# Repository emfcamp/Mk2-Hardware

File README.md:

Hardware
========

Hardware for the TiLDA v2 Badge

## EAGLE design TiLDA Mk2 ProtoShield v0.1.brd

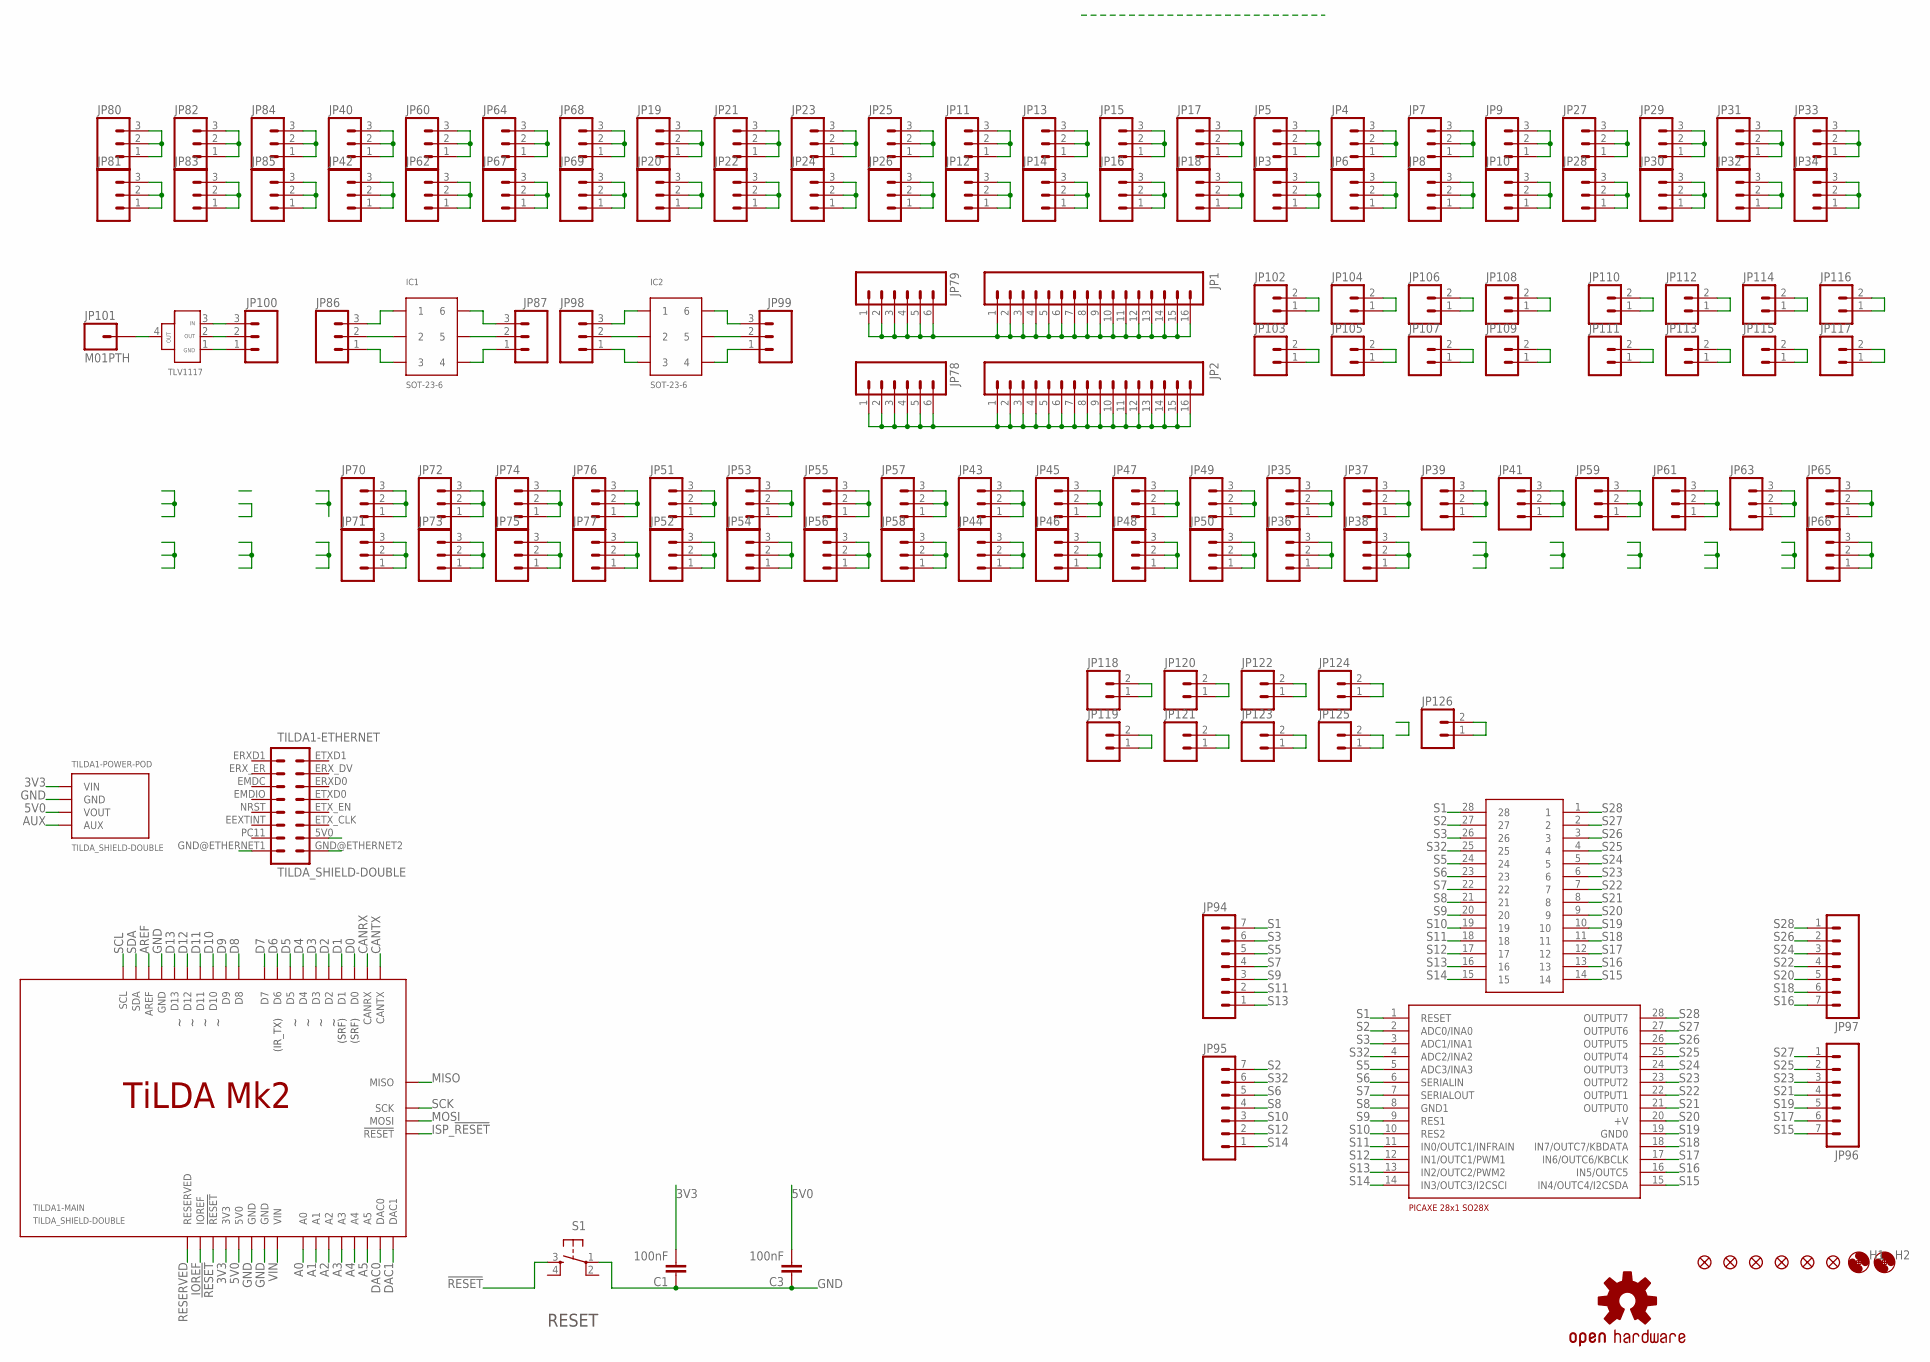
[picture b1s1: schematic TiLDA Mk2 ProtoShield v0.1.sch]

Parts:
C1, C3: 100nF; C025-024X044
FID1, FID2, FID3, FID4, FID5, FID6: FIDUCIAL1X2.5-STOP; FIDUCIAL-1X2.5-STOP
H1, H2: MOUNT-HOLE4.5-LWK; 4,5-LWK
IC1, IC2: SOT-23-6
JP1, JP2: M16PROTO_SILK; 1X16_PROTO_SILK
JP3, JP4, JP5, JP6, JP7, JP8, JP9, JP10, JP11, JP12, JP13, JP14, JP15, JP16, JP17, JP18, JP19, JP20, JP21, JP22, JP23, JP24, JP25, JP26, JP27, JP28, JP29, JP30, JP31, JP32, JP33, JP34, JP35, JP36, JP37, JP38, JP39, JP40, JP41, JP42, JP43, JP44, JP45, JP46, JP47, JP48, JP49, JP50, JP51, JP52, JP53, JP54, JP55, JP56, JP57, JP58, JP59, JP60, JP61, JP62, JP63, JP64, JP65, JP66, JP67, JP68, JP69, JP70, JP71, JP72, JP73, JP74, JP75, JP76, JP77, JP80, JP81, JP82, JP83, JP84, JP85: M03PROTO_SILK; 1X03_PROTO_SILK
JP78, JP79: M06PROTO_SILK; 1X06_PROTO_SLIK
JP86, JP87, JP98, JP99, JP100: M03PTH; 1X03
JP94, JP95, JP96, JP97: M07; 1X07
JP101: M01PTH; 1X01
JP102, JP103, JP104, JP105, JP106, JP107, JP108, JP109, JP110, JP111, JP112, JP113, JP114, JP115, JP116, JP117, JP118, JP119, JP120, JP121, JP122, JP123, JP124, JP125, JP126: M02PROTO_SILK; 1X02_PROTO_SILK
LOGO1: OSHW-LOGOM; OSHW-LOGO-M
LOGO2: EMFLOGO-2014-BOTH; EMFLOGO4
S1: TAC_SWITCHPTH; TACTILE-PTH
TILDA1: TILDA_SHIELD-DOUBLE; TILDA_SHIELD_DOUBLE
U$1: TLV1117-33CDCY; SOT223
U$2: SSOP28-NOSLIK; SSOP28D-NOSILK
U$5: PICAXE-28X1-SO28-MULITWIDE; S028-MUTLIWIDE

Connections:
3V3: C1.2, TILDA1.3V3@1 (3V3), TILDA1.3V3@2 (3V3), TILDA1.3V3@POD (VIN), TILDA1.3V3@POD1 (VIN)
5V0: C3.2, TILDA1.5V (5V0), TILDA1.5V0 (14), TILDA1.5V0@1 (5V0), TILDA1.5V0@POD (VOUT), TILDA1.5V0@POD1 (VOUT), TILDA1.5V@ISP (5V0), TILDA1.5V@ISP@1 (5V0)
!RESET: S1.3, TILDA1.!RESET, TILDA1.!RESET@1 (!RESET)
A0: TILDA1.A0, TILDA1.A0@1 (A0)
A1: TILDA1.A1, TILDA1.A1@1 (A1)
A2: TILDA1.A2, TILDA1.A2@1 (A2)
A3: TILDA1.A3, TILDA1.A3@1 (A3)
A4: TILDA1.A4, TILDA1.A4@1 (A4)
A5: TILDA1.A5, TILDA1.A5@1 (A5)
AREF: TILDA1.AREF, TILDA1.AREF@1 (AREF)
AUX: TILDA1.AUX@POD (AUX), TILDA1.AUX@POD1 (AUX)
CANRX: TILDA1.CANRX, TILDA1.CANRX@1 (CANRX)
CANTX: TILDA1.CANTX, TILDA1.CANTX@1 (CANTX)
D0: TILDA1.D0, TILDA1.D0@1 (D0)
D1: TILDA1.D1, TILDA1.D1@1 (D1)
D2: TILDA1.D2, TILDA1.D2@1 (D2)
D3: TILDA1.D3, TILDA1.D3@1 (D3)
D4: TILDA1.D4, TILDA1.D4@1 (D4)
D5: TILDA1.D5, TILDA1.D5@1 (D5)
D6: TILDA1.D6, TILDA1.D6@1 (D6)
D7: TILDA1.D7, TILDA1.D7@1 (D7)
D8: TILDA1.D8, TILDA1.D8@1 (D8)
D9: TILDA1.D9, TILDA1.D9@1 (D9)
D10: TILDA1.D10, TILDA1.D10@1 (D10)
D11: TILDA1.D11, TILDA1.D11@1 (D11)
D12: TILDA1.D12, TILDA1.D12@1 (D12)
D13: TILDA1.D13, TILDA1.D13@1 (D13)
DAC0: TILDA1.DAC0, TILDA1.DAC0@1 (DAC0)
DAC1: TILDA1.DAC1, TILDA1.DAC1@1 (DAC1)
GND: C1.1, C3.1, S1.1, TILDA1.GND@1 (GND), TILDA1.GND@2 (GND), TILDA1.GND@3 (GND), TILDA1.GND@4 (GND), TILDA1.GND@5 (GND), TILDA1.GND@6 (GND), TILDA1.GND@ETHERNET1 (15), TILDA1.GND@ETHERNET2 (16), TILDA1.GND@ISP (GND), TILDA1.GND@ISP1 (GND), TILDA1.GND@POD (GND), TILDA1.GND@POD1 (GND)
IOREF: TILDA1.IOREF, TILDA1.IOREF@1 (IOREF)
ISP_!RESET: TILDA1.!RESET@ISP (!RESET), TILDA1.!RESET@ISP1 (!RESET)
MISO: TILDA1.MISO, TILDA1.MISO@1 (MISO)
MOSI: TILDA1.MOSI, TILDA1.MOSI@1 (MOSI)
unnamed: JP1.1, JP1.2, JP1.3, JP1.4, JP1.5, JP1.6, JP1.7, JP1.8, JP1.9, JP1.10, JP1.11, JP1.12, JP1.13, JP1.14, JP1.15, JP1.16, JP79.1, JP79.2, JP79.3, JP79.4, JP79.5, JP79.6
unnamed: JP2.1, JP2.2, JP2.3, JP2.4, JP2.5, JP2.6, JP2.7, JP2.8, JP2.9, JP2.10, JP2.11, JP2.12, JP2.13, JP2.14, JP2.15, JP2.16, JP78.1, JP78.2, JP78.3, JP78.4, JP78.5, JP78.6
unnamed: JP5.1, JP5.2, JP5.3
unnamed: JP3.1, JP3.2, JP3.3
unnamed: JP4.1, JP4.2, JP4.3
unnamed: JP6.1, JP6.2, JP6.3
unnamed: JP7.1, JP7.2, JP7.3
unnamed: JP8.1, JP8.2, JP8.3
unnamed: JP9.1, JP9.2, JP9.3
unnamed: JP10.1, JP10.2, JP10.3
unnamed: JP11.1, JP11.2, JP11.3
unnamed: JP12.1, JP12.2, JP12.3
unnamed: JP13.1, JP13.2, JP13.3
unnamed: JP14.1, JP14.2, JP14.3
unnamed: JP15.1, JP15.2, JP15.3
unnamed: JP16.1, JP16.2, JP16.3
unnamed: JP17.1, JP17.2, JP17.3
unnamed: JP18.1, JP18.2, JP18.3
unnamed: JP19.1, JP19.2, JP19.3
unnamed: JP20.1, JP20.2, JP20.3
unnamed: JP21.1, JP21.2, JP21.3
unnamed: JP22.1, JP22.2, JP22.3
unnamed: JP23.1, JP23.2, JP23.3
unnamed: JP24.1, JP24.2, JP24.3
unnamed: JP25.1, JP25.2, JP25.3
unnamed: JP26.1, JP26.2, JP26.3
unnamed: JP27.1, JP27.2, JP27.3
unnamed: JP28.1, JP28.2, JP28.3
unnamed: JP29.1, JP29.2, JP29.3
unnamed: JP30.1, JP30.2, JP30.3
unnamed: JP31.1, JP31.2, JP31.3
unnamed: JP32.1, JP32.2, JP32.3
unnamed: JP33.1, JP33.2, JP33.3
unnamed: JP34.1, JP34.2, JP34.3
unnamed: JP35.1, JP35.2, JP35.3
unnamed: JP36.1, JP36.2, JP36.3
unnamed: JP37.1, JP37.2, JP37.3
unnamed: JP38.1, JP38.2, JP38.3
unnamed: JP39.1, JP39.2, JP39.3
unnamed: JP41.1, JP41.2, JP41.3
unnamed: JP43.1, JP43.2, JP43.3
unnamed: JP44.1, JP44.2, JP44.3
unnamed: JP45.1, JP45.2, JP45.3
unnamed: JP46.1, JP46.2, JP46.3
unnamed: JP47.1, JP47.2, JP47.3
unnamed: JP48.1, JP48.2, JP48.3
unnamed: JP49.1, JP49.2, JP49.3
unnamed: JP50.1, JP50.2, JP50.3
unnamed: JP51.1, JP51.2, JP51.3
unnamed: JP52.1, JP52.2, JP52.3
unnamed: JP53.1, JP53.2, JP53.3
unnamed: JP54.1, JP54.2, JP54.3
unnamed: JP55.1, JP55.2, JP55.3
unnamed: JP56.1, JP56.2, JP56.3
unnamed: JP57.1, JP57.2, JP57.3
unnamed: JP58.1, JP58.2, JP58.3
unnamed: JP59.1, JP59.2, JP59.3
unnamed: JP61.1, JP61.2, JP61.3
unnamed: JP63.1, JP63.2, JP63.3
unnamed: JP65.1, JP65.2, JP65.3
unnamed: JP66.1, JP66.2, JP66.3
unnamed: JP40.1, JP40.2, JP40.3
unnamed: JP42.1, JP42.2, JP42.3
unnamed: JP60.1, JP60.2, JP60.3
unnamed: JP62.1, JP62.2, JP62.3
unnamed: JP64.1, JP64.2, JP64.3
unnamed: JP67.1, JP67.2, JP67.3
unnamed: JP68.1, JP68.2, JP68.3
unnamed: JP69.1, JP69.2, JP69.3
unnamed: JP70.1, JP70.2, JP70.3
unnamed: JP71.1, JP71.2, JP71.3
unnamed: JP72.1, JP72.2, JP72.3
unnamed: JP73.1, JP73.2, JP73.3
unnamed: JP74.1, JP74.2, JP74.3
unnamed: JP75.1, JP75.2, JP75.3
unnamed: JP76.1, JP76.2, JP76.3
unnamed: JP77.1, JP77.2, JP77.3
unnamed: IC1.2, JP86.2
unnamed: IC1.1, JP86.3
unnamed: JP80.1, JP80.2, JP80.3
unnamed: JP81.1, JP81.2, JP81.3
unnamed: JP82.1, JP82.2, JP82.3
unnamed: JP83.1, JP83.2, JP83.3
unnamed: JP84.1, JP84.2, JP84.3
unnamed: JP85.1, JP85.2, JP85.3
unnamed: IC1.3, JP86.1
unnamed: IC1.5, JP87.2
unnamed: IC1.6, JP87.3
unnamed: IC1.4, JP87.1
unnamed: IC2.2, JP98.2
unnamed: IC2.1, JP98.3
unnamed: IC2.3, JP98.1
unnamed: IC2.5, JP99.2
unnamed: IC2.6, JP99.3
unnamed: IC2.4, JP99.1
unnamed: JP100.1, U$1.1 (GND)
unnamed: JP100.2, U$1.2 (OUT1)
unnamed: JP100.3, U$1.3 (IN)
unnamed: JP101.1, U$1.4 (OUT2)
unnamed: JP102.1, JP102.2
unnamed: JP103.1, JP103.2
unnamed: JP104.1, JP104.2
unnamed: JP105.1, JP105.2
unnamed: JP106.1, JP106.2
unnamed: JP107.1, JP107.2
unnamed: JP108.1, JP108.2
unnamed: JP109.1, JP109.2
unnamed: JP110.1, JP110.2
unnamed: JP111.1, JP111.2
unnamed: JP112.1, JP112.2
unnamed: JP113.1, JP113.2
unnamed: JP114.1, JP114.2
unnamed: JP115.1, JP115.2
unnamed: JP116.1, JP116.2
unnamed: JP117.1, JP117.2
unnamed: JP118.1, JP118.2
unnamed: JP119.1, JP119.2
unnamed: JP120.1, JP120.2
unnamed: JP121.1, JP121.2
unnamed: JP122.1, JP122.2
unnamed: JP123.1, JP123.2
unnamed: JP124.1, JP124.2
unnamed: JP125.1, JP125.2
unnamed: JP126.1, JP126.2
RESERVED: TILDA1.RESERVED, TILDA1.RESERVED@1 (RESERVED)
S1: JP94.7, U$2.28, U$5.1 (RESET)
S2: JP95.7, U$2.27, U$5.2 (ADC0/INA0)
S3: JP94.6, U$2.26, U$5.3 (ADC1/INA1)
S5: JP94.5, U$2.24, U$5.5 (ADC3/INA3)
S6: JP95.5, U$2.23, U$5.6 (SERIALIN)
S7: JP94.4, U$2.22, U$5.7 (SERIALOUT)
S8: JP95.4, U$2.21, U$5.8 (GND1)
S9: JP94.3, U$2.20, U$5.9 (RES1)
S10: JP95.3, U$2.19, U$5.10 (RES2)
S11: JP94.2, U$2.18, U$5.11 (IN0/OUTC1/INFRAIN)
S12: JP95.2, U$2.17, U$5.12 (IN1/OUTC1/PWM1)
S13: JP94.1, U$2.16, U$5.13 (IN2/OUTC2/PWM2)
S14: JP95.1, U$2.15, U$5.14 (IN3/OUTC3/I2CSCI)
S15: JP96.7, U$2.14, U$5.15 (IN4/OUTC4/I2CSDA)
S16: JP97.7, U$2.13, U$5.16 (IN5/OUTC5)
S17: JP96.6, U$2.12, U$5.17 (IN6/OUTC6/KBCLK)
S18: JP97.6, U$2.11, U$5.18 (IN7/OUTC7/KBDATA)
S19: JP96.5, U$2.10, U$5.19 (GND0)
S20: JP97.5, U$2.9, U$5.20 (+V)
S21: JP96.4, U$2.8, U$5.21 (OUTPUT0)
S22: JP97.4, U$2.7, U$5.22 (OUTPUT1)
S23: JP96.3, U$2.6, U$5.23 (OUTPUT2)
S24: JP97.3, U$2.5, U$5.24 (OUTPUT3)
S25: JP96.2, U$2.4, U$5.25 (OUTPUT4)
S26: JP97.2, U$2.3, U$5.26 (OUTPUT5)
S27: JP96.1, U$2.2, U$5.27 (OUTPUT6)
S28: JP97.1, U$2.1, U$5.28 (OUTPUT7)
S32: JP95.6, U$2.25, U$5.4 (ADC2/INA2)
SCK: TILDA1.SCK, TILDA1.SCK@1 (SCK)
SCL: TILDA1.SCL, TILDA1.SCL@1 (SCL)
SDA: TILDA1.SDA, TILDA1.SDA@1 (SDA)
VIN: TILDA1.VIN, TILDA1.VIN@1 (VIN)

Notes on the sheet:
RESET

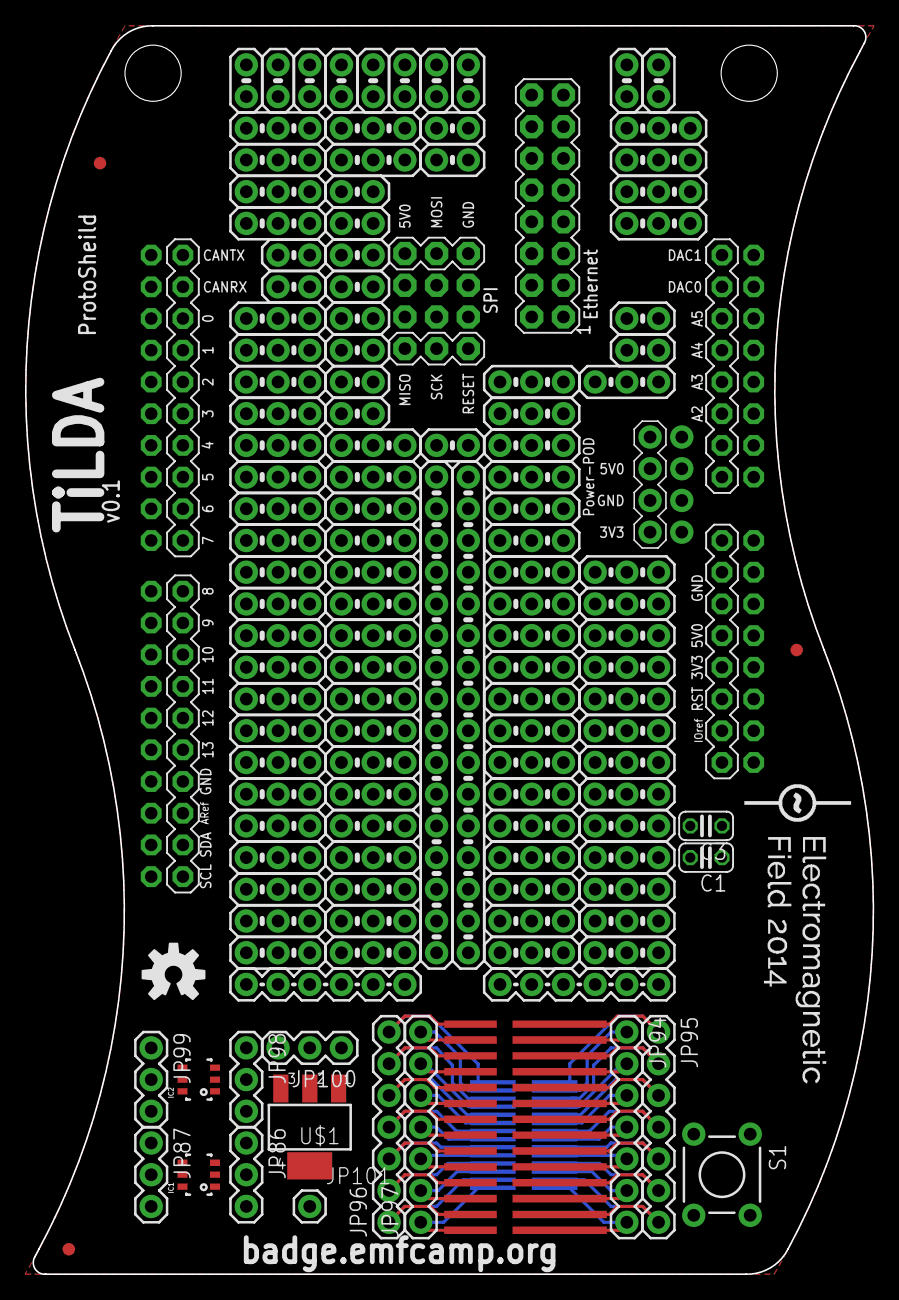
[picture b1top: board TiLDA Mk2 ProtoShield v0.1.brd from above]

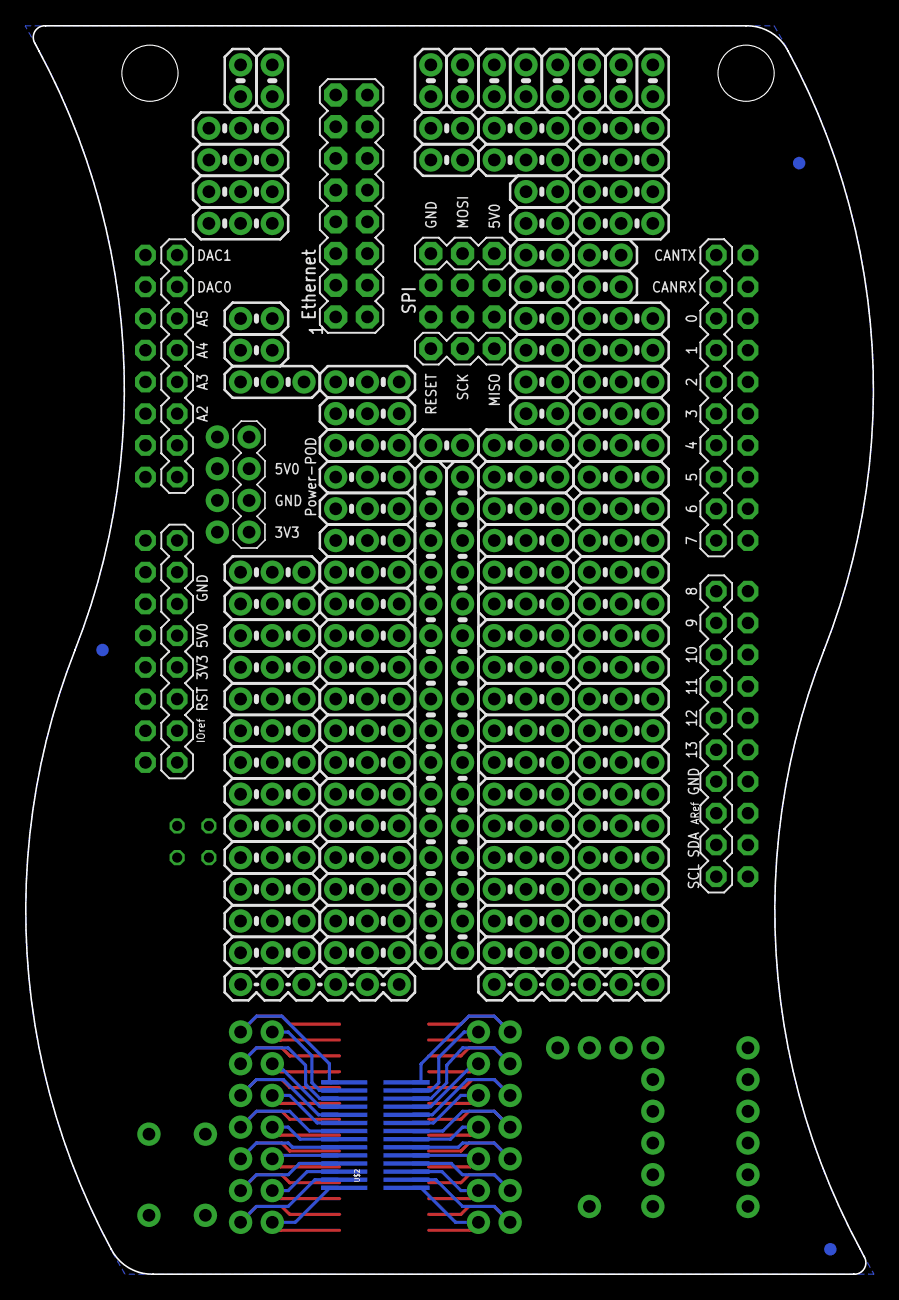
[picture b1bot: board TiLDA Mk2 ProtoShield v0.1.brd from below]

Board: 4 copper layers, 67.9 x 100.0 mm, 139 parts (4 on the bottom side), 191 nets.

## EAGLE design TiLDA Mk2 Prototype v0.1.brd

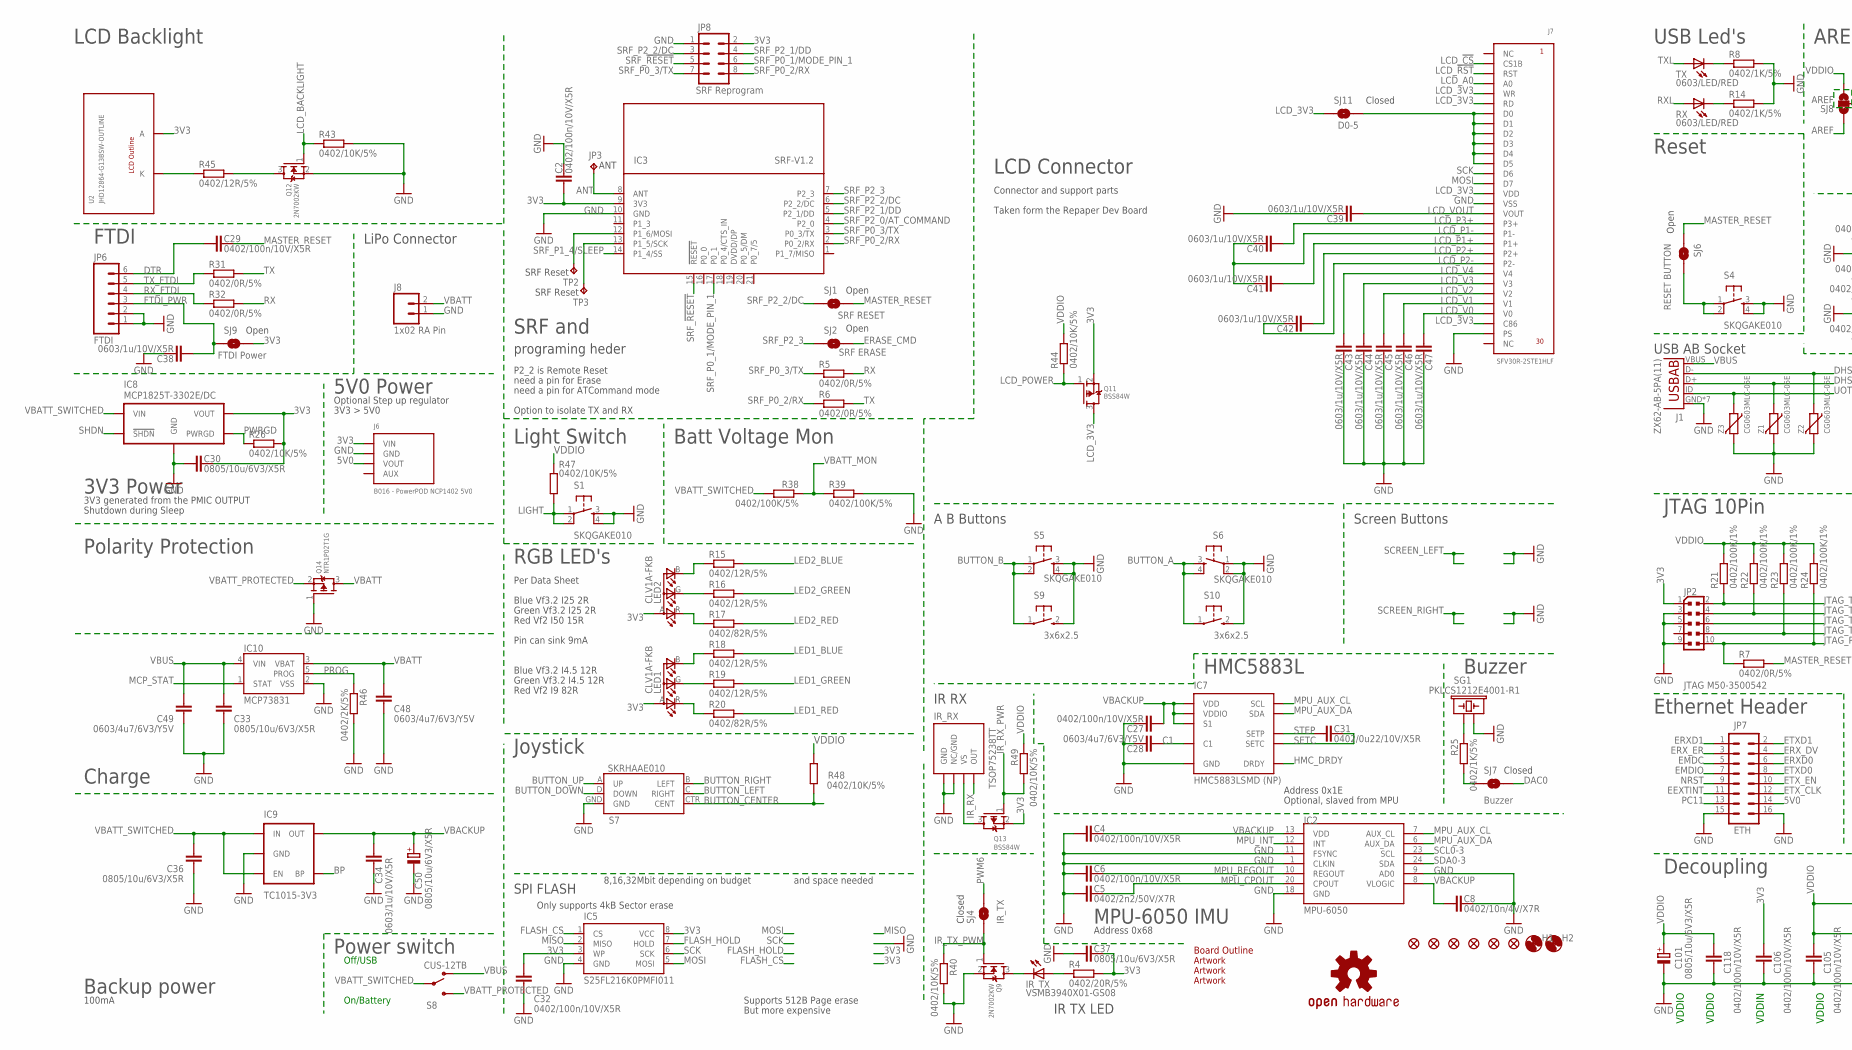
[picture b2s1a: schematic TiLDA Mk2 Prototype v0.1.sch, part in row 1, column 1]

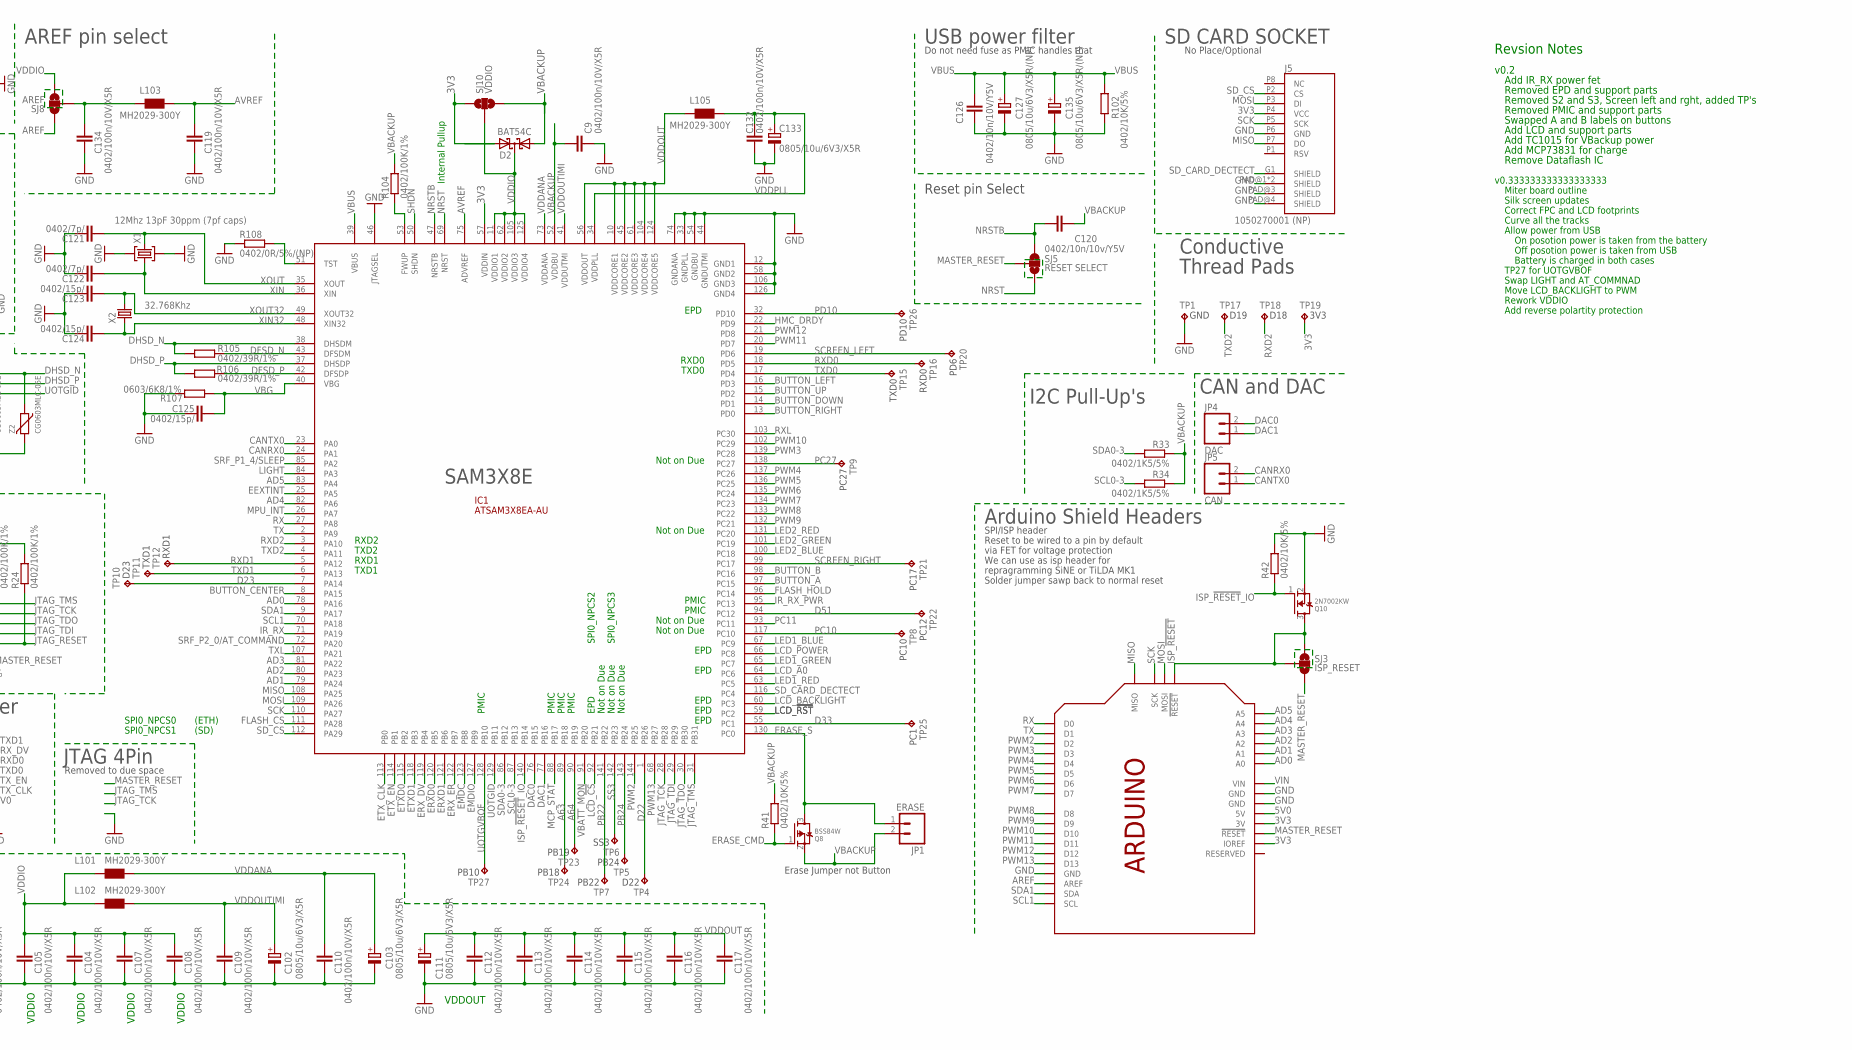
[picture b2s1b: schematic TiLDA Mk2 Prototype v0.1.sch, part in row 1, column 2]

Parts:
ARTWORK1: ARTWORK_FRONT1; TILDA_ARTWORK_FRONT1
ARTWORK2: ARTWORK_ACHIEVEMENT2; TILDA_ARTWORK_ACHIEVEMENT2
ARTWORK3: ARTWORK_ACHIEVEMENT3; TILDA_ARTWORK_ACHIEVEMENT3
C2, C4, C6, C9, C27, C29, C32, C104, C105, C106, C107, C108, C109, C110, C112, C113, C114, C115, C116, C117, C118, C119, C132, C134: 0402/100n/10V/X5R; C0402-ARDUINO-ROUND
C5: 0402/2n2/50V/X7R; C0402-ARDUINO-ROUND
C8: 0402/10n/4V/X7R; C0402-ARDUINO-ROUND
C28, C48, C49: 0603/4u7/6V3/Y5V; C0603-ROUND
C30, C33, C36, C37: 0805/10u/6V3/X5R; C0805RND
C31: 0402/0u22/10V/X5R; C0402-ARDUINO-ROUND
C34, C38, C39, C40, C41, C42, C43, C44, C45, C46, C47: 0603/1u/10V/X5R; C0603-ROUND
C50, C101, C102, C103, C111, C133: 0805/10u/6V3/X5R; C0805RNDPOL
C120: 0402/10n/10v/Y5V; C0402-ARDUINO-ROUND
C121, C122: 0402/7p/; C0402-ARDUINO-ROUND
C123, C124, C125: 0402/15p/; C0402-ARDUINO-ROUND
C126: 0402/10n/10V/Y5V; C0402-ARDUINO-ROUND
C127, C135: 0805/10u/6V3/X5R/(NP); C0805RNDPOL
D2: BAT54C; SOT23
FID1, FID2, FID3, FID4, FID5, FID6: FIDUCIAL1X2.5-STOP; FIDUCIAL-1X2.5-STOP
H1, H2: MOUNT-HOLE4.5-LWK; 4,5-LWK
IC1: ATSAM3X8EA-AU; LQFP144
IC2: MPU-6050; QFN-24-NODIE
IC3: SRF-V1.2; SRF-LANDING-1.2
IC5: S25FL216K0PMFI011; SO08-EIAJ
IC7: HMC5883LSMD (NP); 16LPCC
IC8: MCP1825T-3302E/DC; SOT127P700X180-6N
IC9: TC1015-3V3; SOT23-5
IC10: MCP73831; SOT23-5
IR_RX: TSOP75238TT; TSOP75X
IR_TX: VSMB3940X01-GS08; P-LCC-2
J1: ZX62-AB-5PA(11); USB-AB-MICRO-SMD_LWK
J3: Arduino Headers; ARDUINOR3-LWKTXT-REF-SPI
J5: 1050270001 (NP); 105027-LWK
J6: B016 - PowerPOD NCP1402 5V0; POWER-POD-EMF
J7: SFV30R-2STE1HLF
J8: 1x02 RA Pin; 1X02_RA
JP1: ERASE; 1X02
JP2: JTAG M50-3500542; PINHEAD_2X05_127
JP3: ANT; P1-13
JP4: DAC; 1X02_NO_SILK_OCT
JP5: CAN; 1X02_NO_SILK_OCT
JP6: FTDI; 1X06
JP7: ETH; 2X8
JP8: SRF Reprogram; 2X4-PAD
L101, L102, L103, L105: MH2029-300Y; WUERTH-0805
LED1, LED2: CLV1A-FKB; LED-RGB_CLV1A-FKB
LOGO1: OSHW-LOGOM; OSHW-LOGO-M
OUTLINE1: TILDA_BOARDOUTLINE-MITER; TILDA_BADGEBOARDBARE-VERYWIDE-MITER
Q8, Q11, Q13: BSS84W; SC70-3-R
Q9, Q10, Q12: 2N7002KW; SC70-3-R
Q14: NTR1P02T1G; SOT23-R
R4: 0402/20R/5%; R0402-ARDUINO-ROUND
R5, R6, R7, R31, R32: 0402/0R/5%; R0402-ARDUINO-ROUND
R8, R14, R25: 0402/1K/5%; R0402-ARDUINO-ROUND
R15, R16, R18, R19, R45: 0402/12R/5%; R0402-ARDUINO-ROUND
R17, R20: 0402/82R/5%; R0402-ARDUINO-ROUND
R21, R22, R23, R24, R104: 0402/100K/1%; R0402-ARDUINO-ROUND
R26, R40, R41, R42, R43, R44, R47, R48, R49, R102: 0402/10K/5%; R0402-ARDUINO-ROUND
R33, R34: 0402/1K5/5%; R0402-ARDUINO-ROUND
R38, R39: 0402/100K/5%; R0402-ARDUINO-ROUND
R46: 0402/2K/5%; R0402-ARDUINO-ROUND
R105, R106: 0402/39R/1%; R0402-ARDUINO-ROUND
R107: 0603/6K8/1%; R0603-ROUND
R108: 0402/0R/5%/(NP); R0402-ARDUINO-ROUND
RX: 0603/LED/RED; LED-0805-CORRECT
S1, S4, S5, S6: SKQGAKE010; TACTILE_SWITCH_SMD
S7: SKRHAAE010; JOYSTICK_MULTICOMP
S8: CUS-12TB; SWITCH-SPST-SMD-A
S9, S10: 3x6x2.5; TACTILE_SWITCH_SMD_3X6X2.5H
SG1: PKLCS1212E4001-R1; BUZZER-PKLCS1212E
SJ1: SRF RESET; SJ_2S-NO
SJ2: SRF ERASE; SJ_2S-NO
SJ3: ISP_RESET; SJ_3
SJ4: IR_TX; SJ_2S-TRACE
SJ5: RESET SELECT; SJ_3
SJ6: RESET BUTTON; SJ_2S-NO
SJ7: Buzzer; SJ_2S-TRACE
SJ8: AREF; SJ_3
SJ9: FTDI Power; SJ_2S-NO
SJ10: VDDIO; SJ_3
SJ11: D0-5; SJ_2S-NO
TP1: GND; P1-13
TP2, TP3: SRF Reset; B1,27
TP4: D22; B1,27
TP5: PB24; B1,27
TP6: SS3; B1,27
TP7: PB22; B1,27
TP8: PC10; B1,27
TP9: PC27; B1,27
TP10: D23; B1,27
TP11: TXD1; B1,27
TP12: RXD1; B1,27
TP15: TXD0; B1,27
TP16: RXD0; B1,27
TP17: D19; P1-13
TP18: D18; P1-13
TP19: 3V3; P1-13
TP20: PD6; B1,27
TP21: PC17; B1,27
TP22: PC12; B1,27
TP23: PB19; B1,27
TP24: PB18; B1,27
TP25: PC1; B1,27
TP26: PD10; B1,27
TP27: PB10; B1,27
TX: 0603/LED/RED; LED-0805-CORRECT
U2: JHD12864-G13BSW-OUTLINE
X1: 12Mhz 13pF 30ppm (7pf caps); CRYSTAL-5X3.2
X2: 32.768Khz; RESONATOR_EPSON_FC_145
Z1, Z2, Z3: CG0603MLC-05E; CT/CN0603

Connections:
3V3: C2.2, C30.1, C32.2, C37.1, C106.2, D2.2 (A2), IC1.57 (VDDIN), IC3.9 (3V3), IC5.3 (WP), IC5.8 (VCC), IC8.4 (VOUT), J3.3V, J3.IOREF, J5.P4 (VCC), J6.1 (VIN), JP2.1, JP8.2, LED1.A (ANODE), LED2.A (ANODE), Q11.2 (S), Q13.2 (S), R4.2, R26.2, SJ9.2, SJ10.1, TP19.TP, U2.A
5V0: J3.5V, J3.5V@ISP (5V), J6.3 (VOUT), JP7.14
A63: IC1.89 (PB18), TP24.TP
A64: IC1.90 (PB19), TP23.TP
AD0: IC1.78 (PA16), J3.A0
AD1: IC1.79 (PA24), J3.A1
AD2: IC1.80 (PA23), J3.A2
AD3: IC1.81 (PA22), J3.A3
AD4: IC1.82 (PA6), J3.A4
AD5: IC1.83 (PA4), J3.A5
ANT: IC3.8 (ANT), JP3.TP
AREF: J3.AREF, SJ8.1
AVREF: C119.2, IC1.75 (ADVREF), L103.2
BP: IC9.4 (BP)
BUTTON_A: IC1.97 (PC15), S6.3, S6.4, S10.1
BUTTON_B: IC1.98 (PC16), S5.1, S5.2, S9.1
BUTTON_CENTER: IC1.8 (PA15), R48.1, S7.CTR (CENT)
BUTTON_DOWN: IC1.14 (PD1), S7.D (DOWN)
BUTTON_LEFT: IC1.16 (PD3), S7.C (RIGHT)
BUTTON_RESET: S4.1, S4.2, SJ6.2
BUTTON_RIGHT: IC1.13 (PD0), S7.B (LEFT)
BUTTON_UP: IC1.15 (PD2), S7.A (UP)
BUZZER+: R25.1, SG1.P$1 (1)
BUZZER_RES: R25.2, SJ7.1
C1: C28.2, IC7.10 (C1)
CANRX0: IC1.24 (PA1), JP5.2
CANTX0: IC1.23 (PA0), JP5.1
D22: IC1.1 (PB26), TP4.TP
D23: IC1.7 (PA14), TP10.TP
D33: IC1.55 (PC1), TP25.TP
D51: IC1.94 (PC12), TP22.TP
DAC0: IC1.76 (PB15), JP4.2, SJ7.2
DAC1: IC1.77 (PB16), JP4.1
DFSD_N: IC1.43 (DFSDM), R105.2
DFSD_P: IC1.42 (DFSDP), R106.2
DHSD_N: IC1.38 (DHSDM), J1.D-, R105.1, Z2.1
DHSD_P: IC1.37 (DHSDP), J1.D+, R106.1, Z1.1
DTR: C29.2, JP6.6
EEXTINT: IC1.25 (PA5), JP7.11
EMDC: IC1.123 (PB8), JP7.5
EMDIO: IC1.127 (PB9), JP7.7
ERASE_CMD: Q8.1 (G), R41.1, SJ2.2
ERASE_S: IC1.130 (PC0), JP1.1, Q8.3 (D)
ERXD0: IC1.120 (PB5), JP7.6
ERXD1: IC1.121 (PB6), JP7.1
ERX_DV: IC1.119 (PB4), JP7.4
ERX_ER: IC1.122 (PB7), JP7.3
ETXD0: IC1.115 (PB2), JP7.8
ETXD1: IC1.118 (PB3), JP7.2
ETX_CLK: IC1.113 (PB0), JP7.12
ETX_EN: IC1.114 (PB1), JP7.10
FLASH_CS: IC1.111 (PA28), IC5.1 (CS)
FLASH_HOLD: IC1.96 (PC14), IC5.7 (HOLD)
FTDI_PWR: C38.2, JP6.3, SJ9.1
FWUP: IC1.53 (FWUP), R104.1
GND: C2.1, C4.2, C5.2, C6.2, C8.1, C9.1, C27.1, C28.1, C30.2, C32.1, C33.1, C34.1, C36.1, C37.2, C38.1, C39.1, C43.1, C44.1, C45.1, C46.1, C47.1, C48.1, C49.1, C50.-, C101.-, C102.-, C103.-, C104.1, C105.1, C106.1, C107.1, C108.1, C109.1, C110.1, C111.-, C112.1, C113.1, C114.1, C115.1, C116.1, C117.1, C118.1, C119.1, C121.1, C122.1, C123.1, C124.1, C125.1, C126.2, C127.-, C132.2, C133.-, C134.1, C135.-, IC1.12 (GND1), IC1.33 (GNDPLL), IC1.44 (GNDUTMI), IC1.46 (JTAGSEL), IC1.54 (GNDBU), IC1.58 (GND2), IC1.74 (GNDANA), IC1.106 (GND3), IC1.126 (GND4), IC2.1 (CLKIN), IC2.9 (AD0), IC2.11 (FSYNC), IC2.18 (GND), IC3.10 (GND), IC5.4 (GND), IC7.9 (GND), IC7.11 (GND), IC8.3 (GND), IC8.6 (GND), IC9.2 (GND), IC10.2 (VSS), IR_RX.1 (GND), IR_RX.4 (NC/GND), J1.GND, J1.P$1 (GND), J1.P$2 (GND), J1.P$6 (GND), J1.P$7 (GND), J1.P$8 (GND), J1.P$9 (GND), J3.GND@1 (GND), J3.GND@2 (GND), J3.GND@3 (GND), J3.GND@ISP (GND), J5.P6 (GND), J5.PAD@1 (SHIELD), J5.PAD@2 (SHIELD), J5.PAD@3 (SHIELD), J5.PAD@4 (SHIELD), J6.2 (GND), J7.16 (VSS), J7.29 (PS), J7.M1 (VSS), J7.M2 (VSS), J8.1, JP2.3, JP2.5, JP2.9, JP6.1, JP6.2, JP7.15, JP7.16, JP8.1, Q9.2 (S), Q10.2 (S), Q12.2 (S), Q14.1 (G), R8.2, R14.2, R39.2, R40.2, R42.2, R43.2, R46.2, R102.1, R107.2, R108.1, S1.3, S1.4, S4.3, S4.4, S5.3, S5.4, S6.1, S6.2, S7.GND, S9.2 (3), S10.2 (3), SG1.P$2 (2), TP1.TP, X1.2 (GND), X1.4 (GND), Z1.2, Z2.2, Z3.2
HMC_DRDY: IC1.22 (PD9), IC7.15 (DRDY)
IR_RX: IC1.71 (PA19), IR_RX.3 (OUT)
IR_RX_PWR: IC1.95 (PC13), Q13.1 (G), R49.2
IR_TX_A: IR_TX.A, R4.1
IR_TX_C: IR_TX.C, Q9.3 (D)
IR_TX_PWM: Q9.1 (G), R40.1, SJ4.1
ISP_!RESET: J3.!RESET@ISP (!RESET), Q10.3 (D), SJ3.1, SJ3.2
ISP_!RESET!_IO: IC1.140 (PB14), Q10.1 (G), R42.1
JTAG_RESET: JP2.10, R7.1, R24.1
JTAG_TCK: IC1.28 (PB28), JP2.4, R22.1
JTAG_TDI: IC1.29 (PB29), JP2.8, R23.1
JTAG_TDO: IC1.30 (PB30), JP2.6
JTAG_TMS: IC1.31 (PB31), JP2.2, R21.1
LCD_3V3: J7.5 (WR), J7.6 (RD), J7.15 (VDD), J7.28 (C86), Q11.3 (D), SJ11.1
LCD_!CS: IC1.92 (PB21), J7.2 (CS1B)
LCD_!RST: IC1.59 (PC2), J7.3 (RST)
LCD_A0: IC1.64 (PC6), J7.4 (A0)
LCD_A_SWITCHED: Q12.3 (D), R45.2
LCD_BACKLIGHT: IC1.60 (PC3), Q12.1 (G), R43.1
LCD_P1+: C41.2, J7.20 (P1+)
LCD_P1-: C40.1, C41.1, J7.19 (P1-)
LCD_P2+: C42.2, J7.21 (P2+)
LCD_P2-: C42.1, J7.22 (P2-)
LCD_P3+: C40.2, J7.18 (P3+)
LCD_POWER: IC1.66 (PC8), Q11.1 (G), R44.1
LCD_V0: C47.2, J7.27 (V0)
LCD_V1: C46.2, J7.26 (V1)
LCD_V2: C45.2, J7.25 (V2)
LCD_V3: C44.2, J7.24 (V3)
LCD_V4: C43.2, J7.23 (V4)
LCD_VOUT: C39.2, J7.17 (VOUT)
LED1_BLUE: IC1.67 (PC9), R18.2
LED1_GREEN: IC1.65 (PC7), R19.2
LED1_RED: IC1.63 (PC5), R20.2
LED2_BLUE: IC1.100 (PC18), R15.2
LED2_GREEN: IC1.101 (PC19), R16.2
LED2_RED: IC1.131 (PC20), R17.2
LIGHT: IC1.84 (PA3), R47.1, S1.1, S1.2
MASTER_RESET: C29.1, J3.!RESET, R7.2, SJ1.2, SJ3.3, SJ5.2, SJ6.1
MCP_STAT: IC1.88 (PB17), IC10.1 (STAT)
MISO: IC1.108 (PA25), IC5.2 (MISO), J3.MISO, J5.P7 (DO)
MOSI: IC1.109 (PA26), IC5.5 (MOSI), J3.MOSI, J5.P3 (DI), J7.14 (D7)
MPU_AUX_CL: IC2.7 (AUX_CL), IC7.1 (SCL)
MPU_AUX_DA: IC2.6 (AUX_DA), IC7.16 (SDA)
MPU_CPOUT: C5.1, IC2.20 (CPOUT)
MPU_INT: IC1.26 (PA7), IC2.12 (INT)
MPU_REGOUT: C6.1, IC2.10 (REGOUT)
unnamed: R45.1, U2.K
unnamed: R8.1, TX.C
unnamed: R14.1, RX.C
unnamed: J7.7 (D0), J7.8 (D1), J7.9 (D2), J7.10 (D3), J7.11 (D4), J7.12 (D5), SJ11.2
unnamed: LED1.R (CRED), R20.1
unnamed: LED1.G (CGREEN), R19.1
unnamed: LED1.B (CBLUE), R18.1
unnamed: LED2.R (CRED), R17.1
unnamed: LED2.G (CGREEN), R16.1
unnamed: C134.2, L103.1, SJ8.2
unnamed: LED2.B (CBLUE), R15.1
unnamed: IR_RX.2 (VS), Q13.3 (D)
unnamed: IC3.12 (P1_6/MOSI), TP2.TP
unnamed: IC3.13 (P1_5/SCK), TP3.TP
NRST: IC1.69 (NRST), JP7.9, SJ5.3
NRSTB: C120.2, IC1.47 (NRSTB), SJ5.1
PB22: IC1.141 (PB22), TP7.TP
PB24: IC1.143 (PB24), TP5.TP
PC10: IC1.117 (PC10), TP8.TP
PC11: IC1.93 (PC11), JP7.13
PC27: IC1.138 (PC27), TP9.TP
PD10: IC1.32 (PD10), TP26.TP
PROG: IC10.5 (PROG), R46.1
PWM2: IC1.144 (PB25), J3.D2
PWM3: IC1.139 (PC28), J3.D3
PWM4: IC1.137 (PC26), J3.D4
PWM5: IC1.136 (PC25), J3.D5
PWM6: IC1.135 (PC24), J3.D6, SJ4.2
PWM7: IC1.134 (PC23), J3.D7
PWM8: IC1.133 (PC22), J3.D8
PWM9: IC1.132 (PC21), J3.D9
PWM10: IC1.102 (PC29), J3.D10
PWM11: IC1.20 (PD7), J3.D11
PWM12: IC1.21 (PD8), J3.D12
PWM13: IC1.68 (PB27), J3.D13
PWRGD: IC8.5 (PWRGD), R26.1
RX: IC1.27 (PA8), J3.D0, R5.2, R32.2
RXD0: IC1.18 (PD5), TP16.TP
RXD1: IC1.5 (PA12), TP12.TP
RXD2: IC1.3 (PA10), TP18.TP
RXL: IC1.103 (PC30), RX.A
RX_FTDI: JP6.4, R32.1
SCK: IC1.110 (PA27), IC5.6 (SCK), J3.SCK, J5.P5 (SCK), J7.13 (D6)
SCL0-3: IC1.87 (PB13), IC2.23 (SCL), R34.2
SCL1: IC1.70 (PA18), J3.SCL
SCREEN_LEFT: IC1.19 (PD6), TP20.TP
SCREEN_RIGHT: IC1.99 (PC17), TP21.TP
SDA0-3: IC1.86 (PB12), IC2.24 (SDA), R33.2
SDA1: IC1.9 (PA17), J3.SDA
SD_CARD_DECTECT: IC1.116 (PC4), J5.G1 (SHIELD)
SD_CS: IC1.112 (PA29), J5.P2 (CS)
SETC: C31.1, IC7.12 (SETC)
SHDN: IC1.50 (SHDN), IC8.1 (!SHDN)
SRF_!RESET: IC3.15 (!RESET), JP8.5
SRF_P0_1/MODE_PIN_1: IC3.17 (P0_1), JP8.6
SRF_P0_2/RX: IC3.2 (P0_2/RX), JP8.8, R6.1
SRF_P0_3/TX: IC3.3 (P0_3/TX), JP8.7, R5.1
SRF_P1_4/SLEEP: IC1.85 (PA2), IC3.14 (P1_4/SS)
SRF_P2_0/AT_COMMAND: IC1.72 (PA20), IC3.4 (P2_0)
SRF_P2_1/DD: IC3.5 (P2_1/DD), JP8.4
SRF_P2_2/DC: IC3.6 (P2_2/DC), JP8.3, SJ1.1
SRF_P2_3: IC3.7 (P2_3), SJ2.1
SS3: IC1.142 (PB23), TP6.TP
STEP: C31.2, IC7.8 (SETP)
TST: IC1.51 (TST), R108.2
TX: IC1.2 (PA9), J3.D1, R6.2, R31.2
TXD0: IC1.17 (PD4), TP15.TP
TXD1: IC1.6 (PA13), TP11.TP
TXD2: IC1.4 (PA11), TP17.TP
TXL: IC1.107 (PA21), TX.A
TX_FTDI: JP6.5, R31.1
UOTGID: IC1.129 (PB11), J1.ID (USBID), Z3.1
UOTGVBOF: IC1.128 (PB10), TP27.TP
VBACKUP: C4.1, C8.2, C9.2, C27.2, C34.2, C50.+, C120.1, D2.1 (A1), IC1.52 (VDDBU), IC2.8 (VLOGIC), IC2.13 (VDD), IC7.2 (VDD), IC7.4 (S1), IC7.13 (VDDIO), IC9.5 (OUT), JP1.2, Q8.2 (S), R33.1, R34.1, R41.2, R104.2, SJ10.3
VBATT: C48.2, IC10.3 (VBAT), J8.2, Q14.3 (D)
VBATT_MON: IC1.91 (PB20), R38.1, R39.1
VBATT_PROTECTED: Q14.2 (S), S8.3 (S)
VBATT_SWITCHED: C36.2, IC8.2 (VIN), IC9.1 (IN), IC9.3 (EN), R38.2, S8.2
VBG: C125.2, IC1.40 (VBG), R107.1
VBUS: C33.2, C49.2, C126.1, C127.+, C135.+, IC1.39 (VBUS), IC10.4 (VIN), J1.VBUS, R102.2, S8.1 (O); also elsewhere on the board
VDDANA: C103.+, C110.2, IC1.73 (VDDANA), L101.2
VDDIO: C101.+, C104.2, C105.2, C107.2, C108.2, C118.2, D2.3 (CC), IC1.11 (VDDIO1), IC1.62 (VDDIO2), IC1.105 (VDDIO3), IC1.125 (VDDIO4), L101.1, L102.1, R21.2, R22.2, R23.2, R24.2, R44.2, R47.2, R48.2, R49.1, SJ8.3, SJ10.2
VDDOUT: C111.+, C112.2, C113.2, C114.2, C115.2, C116.2, C117.2, IC1.10 (VDDCORE1), IC1.45 (VDDCORE2), IC1.56 (VDDOUT), IC1.61 (VDDCORE3), IC1.104 (VDDCORE4), IC1.124 (VDDCORE5), L105.1
VDDOUTIMI: C102.+, C109.2, IC1.41 (VDDUTMI), L102.2
VDDPLL: C132.1, C133.+, IC1.34 (VDDPLL), L105.2
VIN: J3.VIN
XIN: C122.2, IC1.36 (XIN), X1.1 (C1)
XIN32: C124.2, IC1.48 (XIN32), X2.P$1 (1)
XOUT: C121.2, IC1.35 (XOUT), X1.3 (C2)
XOUT32: C123.2, IC1.49 (XOUT32), X2.P$2 (2)

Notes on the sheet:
Reset to be wired to a pin by default
We can use as isp header for
Solder jumper sawp back to normal reset
LCD Backlight
LCD Connector
P2_2 is Remote Reset
Taken form the Repaper Dev Board
SRF and
Connector and support parts
programing heder
need a pin for ATCommand mode
Address 0x68
MPU-6050 IMU
Internal Pullup
need a pin for Erase
8,16,32Mbit depending on budget
Erase Jumper not Button
(ETH)
(SD)
FTDI
Option to isolate TX and RX
SPI FLASH
and space needed
Arduino Shield Headers
SPI/ISP header
repragramming SiNE or TiLDA MK1
SPI0_NPCS0
SPI0_NPCS1
SPI0_NPCS2
SPI0_NPCS3
CAN and DAC
RGB LED's
IR TX LED
IR RX
Light Switch
SD CARD SOCKET
USB Led's
Reset
Screen Buttons
Red Vf2 I50 15R
